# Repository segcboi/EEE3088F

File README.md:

# EEE3088F Group 9 Micro-Mouse Power Subsystem 

The object of this project is to design a power subsystem that will be able to power a multitude of functions of a maze-solving Micro-Mouse for our EEE3088F Engineering Design Principles course.  

## Requirements
- Operate four motors bidirectionally
- Monitor battery using the INA219
- Charge the battery using 9 V
- Have both 200 mA and 600 mA charging modes
- Provide 3V3 and 5V
- Integrate a USB-C port for charging
- Provide external load switching
- Provide a switch to turn off the system

## Layout
The layout of files for the project are as follows:
### Datasheets
This is where all component datasheets are located.
### Power_Board_v2
This is whare the PCB schematics and design are located
### Library.pretty
This is where certain components's footprints can be located, mainly the switch and __________ since KiCad had no stored footprint for the required switch and_________.

## External Sources
Certain external sources were used to make life and the design process slightly easier. These included
- Bouni's Repo: This gave access to a multitude of features that allowed KiCad access to a whole host of components from JLCPCB's parts library.
- The devil: We sold our souls to the devil himself to actually get this design completed.

## Design Tools
The design of the PCB was done using the free PCB desgin software KiCad.

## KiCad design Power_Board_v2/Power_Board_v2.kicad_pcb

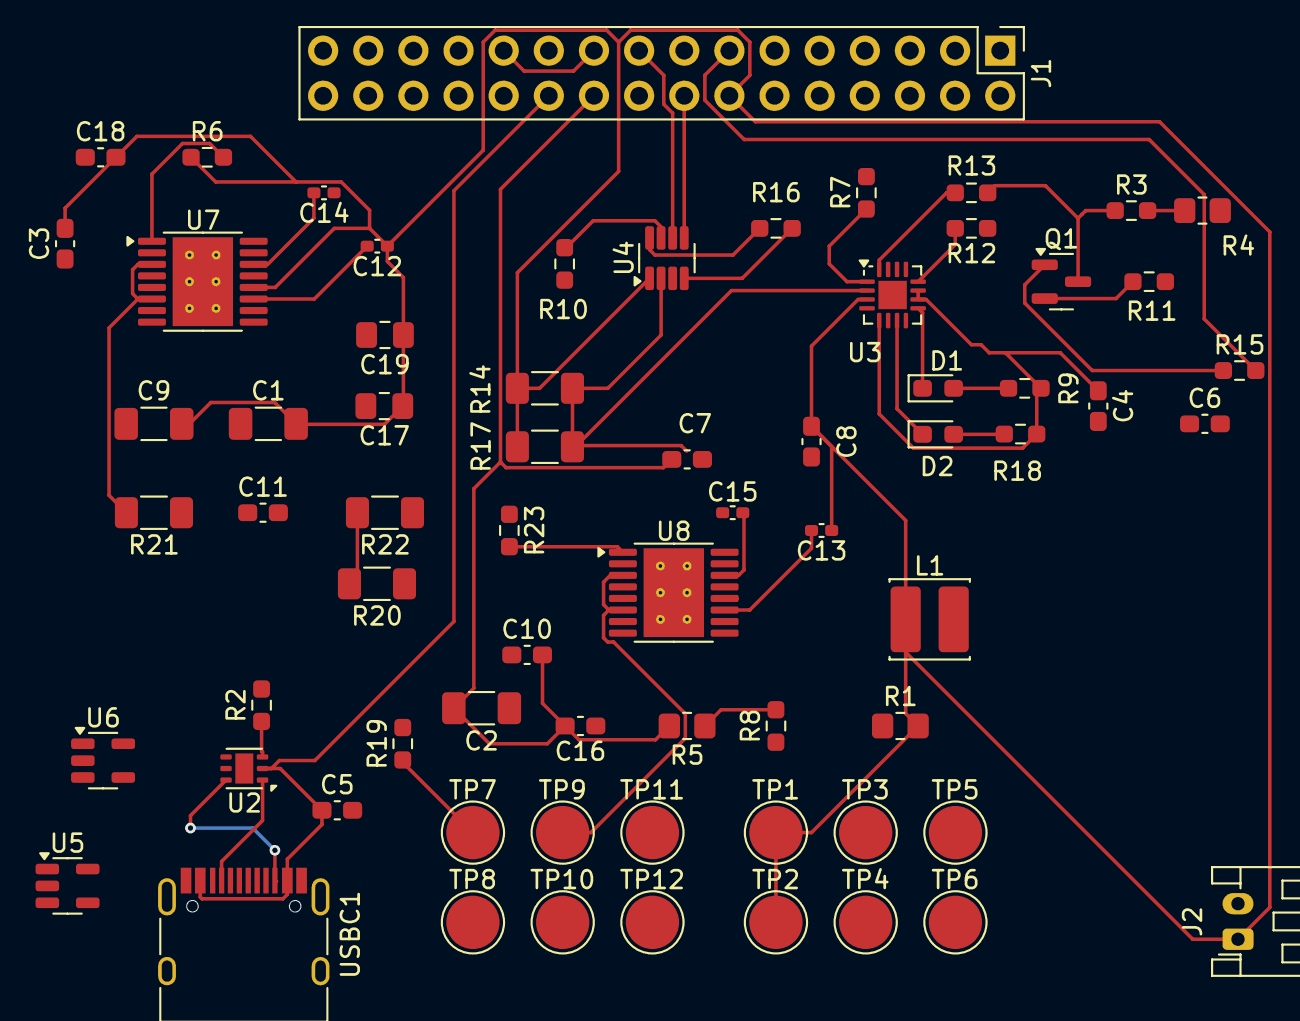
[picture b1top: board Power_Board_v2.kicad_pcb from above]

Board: 2 copper layers, 68 parts (0 on the bottom side), 52 nets.

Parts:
C1, C2: 22uF; C_1206_3216Metric_Pad1.33x1.80mm_HandSolder
C3, C11: 4.7uF; C_0603_1608Metric_Pad1.08x0.95mm_HandSolder
C4, C8: 4.7u; C_0603_1608Metric_Pad1.08x0.95mm_HandSolder
C5, C6, C7: 1u; C_0603_1608Metric_Pad1.08x0.95mm_HandSolder
C9: 100uF; C_1206_3216Metric_Pad1.33x1.80mm_HandSolder
C10, C16, C18: 1uF; C_0603_1608Metric_Pad1.08x0.95mm_HandSolder
C12, C13: 10nF; C_0402_1005Metric_Pad0.74x0.62mm_HandSolder
C14, C15: 2.2uF; C_0402_1005Metric_Pad0.74x0.62mm_HandSolder
C17, C19: 10uF; C_0805_2012Metric_Pad1.18x1.45mm_HandSolder
D1: LEDW; LED_0603_1608Metric_Pad1.05x0.95mm_HandSolder
D2: LEDR; LED_0603_1608Metric_Pad1.05x0.95mm_HandSolder
J1: PH2.54-01-16PZS; PinHeader_2x16_P2.54mm_Vertical
J2: Conn_01x02; JST_PH_S2B-PH-K_1x02_P2.00mm_Horizontal
L1: SWPA4020S1R5NT; L_Cenker_CKCS4018
Q1: MMBT5551L; SOT-23
R1, R5: 1MΩ; R_0805_2012Metric_Pad1.20x1.40mm_HandSolder
R2: 75k; R_0603_1608Metric_Pad0.98x0.95mm_HandSolder
R3: 4k3; R_0603_1608Metric_Pad0.98x0.95mm_HandSolder
R4: 150R; R_0805_2012Metric_Pad1.20x1.40mm_HandSolder
R6, R19, R23: 10kΩ; R_0603_1608Metric_Pad0.98x0.95mm_HandSolder
R7, R10, R16: 10k; R_0603_1608Metric_Pad0.98x0.95mm_HandSolder
R8: 330kΩ; R_0603_1608Metric_Pad0.98x0.95mm_HandSolder
R9, R11, R12, R13, R15, R18: 1k5; R_0603_1608Metric_Pad0.98x0.95mm_HandSolder
R14, R17: 0.4R; R_1206_3216Metric_Pad1.30x1.75mm_HandSolder
R20, R21, R22: 1Ω; R_1206_3216Metric_Pad1.30x1.75mm_HandSolder
TP1, TP2, TP3, TP4, TP5, TP6, TP7, TP8, TP9, TP10, TP11, TP12: TestPoint; TestPoint_Pad_D3.0mm
U2: HUSB237-AA001-DN06R; DFN-6-1EP_2x2mm_P0.65mm_EP1.01x1.7mm
U3: BQ24074RGT; VQFN-16-1EP_3x3mm_P0.5mm_EP1.6x1.6mm
U4: INA219AIDCNR; SOT-23-8
U5, U6: RT9742GGJ5; TSOT-23-5
U7, U8: DRV8833PWP; HTSSOP-16-1EP_4.4x5mm_P0.65mm_EP3.4x5mm_Mask2.46x2.31mm_The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
USBC1: TYPE-C-31-M-12; USB_C_Receptacle_HRO_TYPE-C-31-M-12

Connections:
/3V3 Out: C11.2, J1.18
/5V Out: C2.2, C7.1, C10.2, C16.2, J1.20, R5.2, R16.1, U4.4 (VS)
/Battery: C1.2, C3.2, C8.2, C9.2, C12.1, C13.1, C17.1, C18.2, C19.1, J1.14, J2.1, L1.1, R1.2, R6.1, R14.1, R14.2, R17.1, R17.2, R23.1, TP1.1, TP2.1, U3.2 (BAT), U3.3 (BAT), U4.1 (IN+), U4.2 (IN-), U7.12 (VM), U8.12 (VM)
/FAST_CHARGE_CTRL: J1.13, R15.2
/High Voltage (9V): C5.1, C6.1, J1.22, U2.2 (VUSB), U3.13 (IN), USBC1.A4 (VBUS), USBC1.A9 (VBUS), USBC1.B4 (VBUS), USBC1.B9 (VBUS)
/I2C1_SCL: J1.16, U4.5 (SCL)
/I2C1_SDA: J1.17, U4.6 (SDA)
/LOAD: C4.1, R9.1, R18.1, U3.5 (EN2), U3.10 (OUT), U3.11 (OUT)
/MOTOR1_A_OUT: J1.32, U7.2 (AOUT1)
/MOTOR1_B_OUT: J1.31, U7.4 (AOUT2)
/MOTOR1_CTRL1: J1.28, U7.16 (AIN1)
/MOTOR1_CTRL2: J1.30, U7.15 (AIN2)
/MOTOR2_CTRL1: J1.4, U7.9 (BIN1)
/MOTOR2_CTRL2: J1.6, U7.10 (BIN2)
/MOTOR3_A_OUT: J1.27, U8.2 (AOUT1)
/MOTOR3_B_OUT: J1.29, U8.4 (AOUT2)
/MOTOR3_CTRL1: J1.24, U8.16 (AIN1)
/MOTOR3_CTRL2: J1.26, U8.15 (AIN2)
/MOTOR4_CTRL1: J1.8, U8.9 (BIN1)
/MOTOR4_CTRL2: J1.10, U8.10 (BIN2)
/Motor2_A_OUT: J1.2, U7.7 (BOUT1)
/Motor2_B_OUT: J1.1, U7.5 (BOUT2)
/Motor4_A_OUT: J1.3, U8.7 (BOUT1)
/Motor4_B_OUT: J1.5, U8.5 (BOUT2)
GND: C1.1, C2.1, C3.1, C4.2, C5.2, C7.2, C8.1, C9.1, C10.1, C11.1, C14.1, C15.1, C16.1, C17.2, C18.1, C19.2, J1.19, J1.23, J2.2, R1.1, R2.2, R4.2, R7.2, R8.1, R10.2, R11.2, R12.1, R19.2, R20.1, R21.1, R22.1, TP4.1, TP8.1, TP10.1, TP12.1, U2.7 (GND), U3.8 (VSS), U3.17 (VSS), U4.3 (GND), U7.13 (GND), U7.17 (GND), U8.13 (GND), U8.17 (GND), USBC1.A1 (GND), USBC1.A12 (GND), USBC1.B1 (GND), USBC1.B12 (GND)
unnamed: D1.2 (A), R9.2
unnamed: D1.1 (K), U3.9 (~CHG)
unnamed: D2.2 (A), R18.2
unnamed: D2.1 (K), U3.7 (~PGOOD)
unnamed: Q1.1 (B), R15.1
unnamed: Q1.3 (C), R3.1, R13.1, TP3.1
unnamed: Q1.2 (E), R11.1, TP5.1
unnamed: R3.2, R4.1
unnamed: R19.1, TP7.1
unnamed: R5.1, R8.2
unnamed: U2.1 (CC1), USBC1.A5 (CC1)
unnamed: U2.6 (CC2), USBC1.B5 (CC2)
unnamed: R2.1, U2.3 (VSET)
unnamed: C6.2, TP6.1, U3.4 (~CE), U3.6 (EN1), U3.14 (TMR)
unnamed: R12.2, U3.12 (ILIM)
unnamed: R13.2, U3.16 (ISET)
unnamed: R7.1, U3.1 (TS)
unnamed: R10.1, U4.7 (A0)
unnamed: R16.2, U4.8 (A1)
unnamed: R21.2, TP11.1, U7.3 (AISEN), U7.6 (BISEN)
unnamed: C12.2, U7.11 (VCP)
unnamed: C14.2, U7.14 (VINT)
unnamed: R6.2, U7.1 (~SLEEP)
unnamed: R20.2, R22.2, TP9.1, U8.3 (AISEN), U8.6 (BISEN)
unnamed: C13.2, U8.11 (VCP)
unnamed: C15.2, U8.14 (VINT)
unnamed: R23.2, U8.1 (~SLEEP)

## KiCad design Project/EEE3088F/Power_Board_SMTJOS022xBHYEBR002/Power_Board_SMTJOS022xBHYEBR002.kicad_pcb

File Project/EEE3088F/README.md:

# EEE3088F
projekt

This is the repo containing all files and documentation for EEE3088F design projekt.

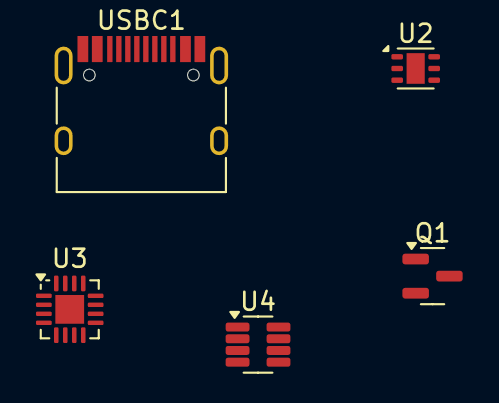
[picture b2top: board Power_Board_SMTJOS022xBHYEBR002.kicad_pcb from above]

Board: 2 copper layers, 5 parts (0 on the bottom side), 5 nets, no tracks yet.

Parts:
Q1: MMBT5551L; SOT-23
U2: HUSB237-AA001-DN06R; DFN-6-1EP_2x2mm_P0.65mm_EP1.01x1.7mm
U3: BQ24074RGT; VQFN-16-1EP_3x3mm_P0.5mm_EP1.6x1.6mm
U4: INA219AxDCN SOT-23; SOT-23-8
USBC1: USB_C_Receptacle_HRO_TYPE-C-31-M-12

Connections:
/BATT: U3.2 (BAT), U3.3 (BAT), U4.2 (IN-)
/HV: U2.2 (VUSB), U3.13 (IN), USBC1.B4 (VBUS), USBC1.B9 (VBUS)
/LOAD: U3.10 (OUT), U3.11 (OUT)
GND: U2.1 (CC1), U2.6 (CC2), U2.7 (GND), U3.4 (~CE), U3.6 (EN1), U3.8 (VSS), U3.14 (TMR), U3.17 (VSS), U4.3 (GND), USBC1.A1 (GND), USBC1.A5 (CC1), USBC1.A12 (GND), USBC1.B1 (GND), USBC1.B5 (CC2), USBC1.B12 (GND)
unnamed: Q1.3 (C), U3.16 (ISET)

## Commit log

2025-03-27 Added my schematic files via upload
2025-03-27 Full project upload with biased ICs and feet
2025-03-27 Power Board v2 upload
    This upload is just an updated Power Board schematic because the PCB editor was tweaking and not displaying the footprints
2025-03-27 Moved Stuff
2025-03-27 Removed and Moved some items
2025-03-27 Removed some duplicates
2025-03-27 Misc
2025-03-27 misc.
2025-03-27 Delete Project directory
    This was nonsense and needed to be removed
2025-03-27 Delete Power_Board_SMTJOS022xBHYEBR002 directory
    Yes
2025-03-27 Pushed files
2025-03-27 Test
2025-03-28 Did some PCB work
2025-03-28 More PCB work
2025-03-28 Space Saving
    Moved my things around to make space for Ebi's work
2025-03-28 Fixed up some errors
2025-03-28 Updated footprints and battery label
    I HATE THE IMPERIAL SYSTEM
2025-03-28 Updated parts' details to get correct BOM
2025-03-28 Same as previous
2025-03-28 Updated some stuffs
    Tried to add the battery connector, but it wouldn't work
2025-03-28 Minor tweaks
2025-03-28 final upload of wtv with feet
2025-03-28 Library.pretty
2025-03-28 gyugyu
2025-03-28 idek
2025-03-28 STARTED EBI WIRING
2025-03-28 STARTED EBI WIRING 2
2025-03-28 yes 3
2025-03-28 Libby-pretty update
2025-03-28 Connected up the last passive stuff
2025-05-13 Update README.md
    This was updated to include more details of our project
2025-05-13 Update README.md
    I gave up
